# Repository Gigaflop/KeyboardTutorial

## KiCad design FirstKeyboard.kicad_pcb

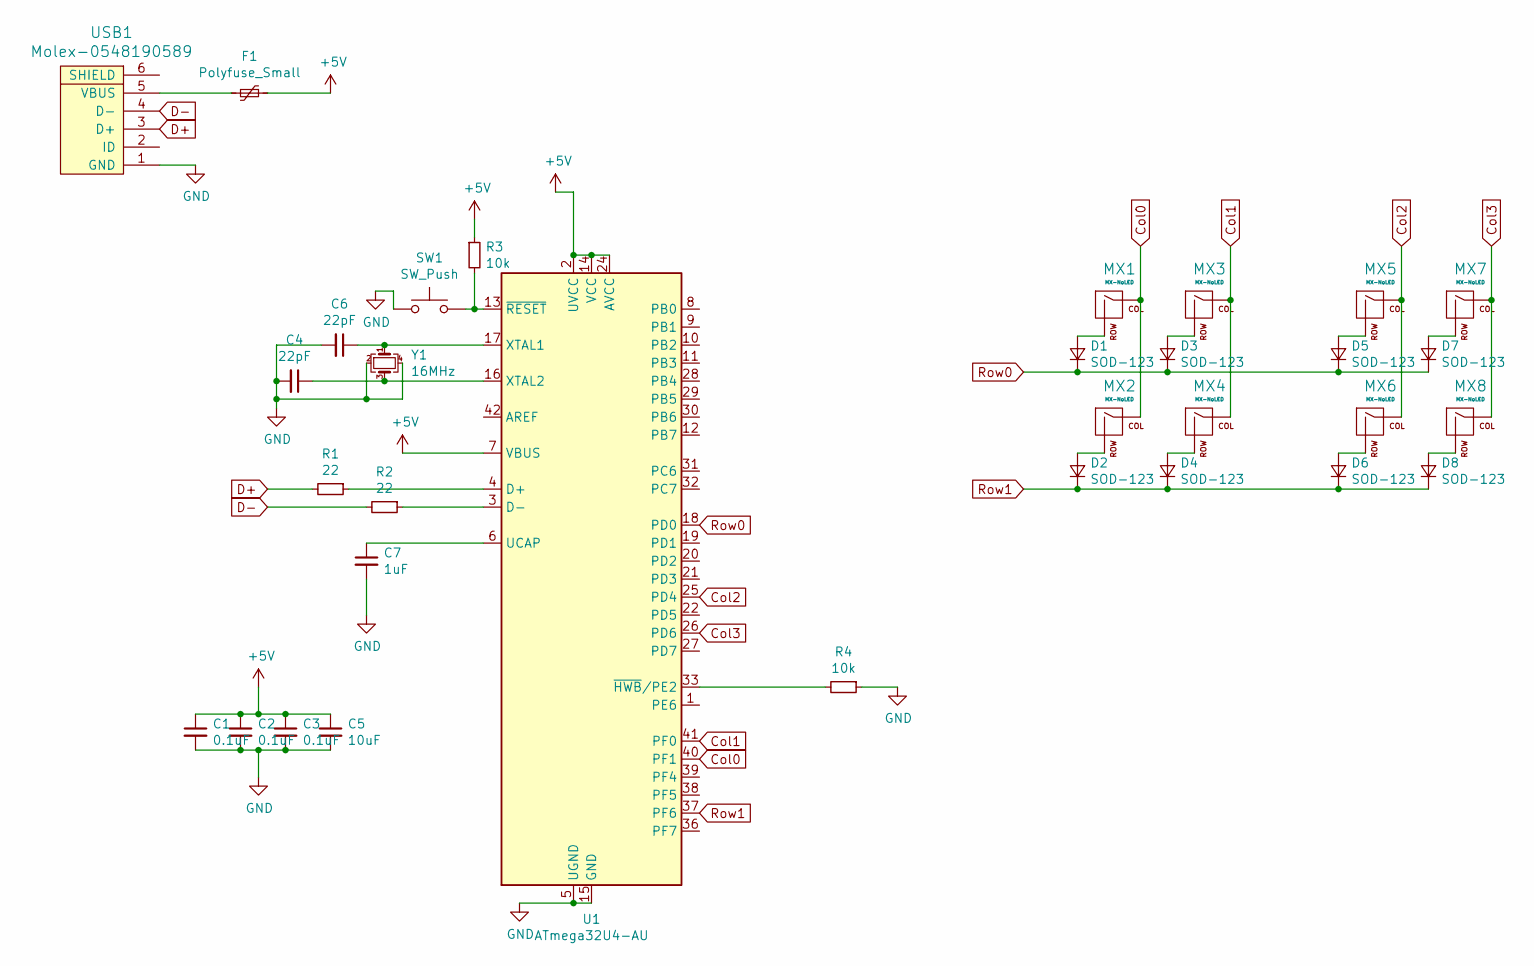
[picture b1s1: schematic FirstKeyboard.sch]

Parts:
C1, C2, C3: 0.1uF; C_0805_2012Metric
C4, C6: 22pF; C_0805_2012Metric
C5: 10uF; C_0805_2012Metric
C7: 1uF; C_0805_2012Metric
D1, D2, D3, D4, D5, D6, D7, D8: SOD-123; D_SOD-123
F1: Polyfuse_Small; Fuse_1206_3216Metric
MX1, MX2, MX3, MX4, MX5, MX6, MX7, MX8: MX-NoLED; MX-1U-NoLED
R1, R2: 22; R_0805_2012Metric
R3, R4: 10k; R_0805_2012Metric
SW1: SW_Push; SKQG-1155865
U1: ATmega32U4-AU; TQFP-44_10x10mm_P0.8mm
USB1: Molex-0548190589
Y1: 16MHz; Crystal_SMD_3225-4Pin_3.2x2.5mm

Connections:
+5V: C1.1, C2.1, C3.1, C5.1, F1.1, R3.1, U1.2 (UVCC), U1.7 (VBUS), U1.14 (VCC), U1.24 (AVCC), U1.34 (VCC), U1.44 (AVCC)
Col0: MX1.1 (COL), MX2.1 (COL), U1.40 (PF1)
Col1: MX3.1 (COL), MX4.1 (COL), U1.41 (PF0)
Col2: MX5.1 (COL), MX6.1 (COL), U1.25 (PD4)
Col3: MX7.1 (COL), MX8.1 (COL), U1.26 (PD6)
D+: R1.2, USB1.3 (D+)
D-: R2.2, USB1.4 (D-)
GND: C1.2, C2.2, C3.2, C4.2, C5.2, C6.2, C7.2, R4.1, SW1.1, U1.5 (UGND), U1.15 (GND), U1.23 (GND), U1.35 (GND), U1.43 (GND), USB1.1 (GND), Y1.2, Y1.4
unnamed: C4.1, U1.16 (XTAL2), Y1.3
unnamed: C6.1, U1.17 (XTAL1), Y1.1
unnamed: C7.1, U1.6 (UCAP)
unnamed: D1.2 (A), MX1.2 (ROW)
unnamed: D2.2 (A), MX2.2 (ROW)
unnamed: D3.2 (A), MX3.2 (ROW)
unnamed: D4.2 (A), MX4.2 (ROW)
unnamed: D5.2 (A), MX5.2 (ROW)
unnamed: D6.2 (A), MX6.2 (ROW)
unnamed: D7.2 (A), MX7.2 (ROW)
unnamed: D8.2 (A), MX8.2 (ROW)
unnamed: F1.2, USB1.5 (VBUS)
unnamed: R1.1, U1.4 (D+)
unnamed: R2.1, U1.3 (D-)
unnamed: R3.2, SW1.2, U1.13 (~RESET)
unnamed: R4.2, U1.33 (~HWB~/PE2)
Row0: D1.1 (K), D3.1 (K), D5.1 (K), D7.1 (K), U1.18 (PD0)
Row1: D2.1 (K), D4.1 (K), D6.1 (K), D8.1 (K), U1.37 (PF6)

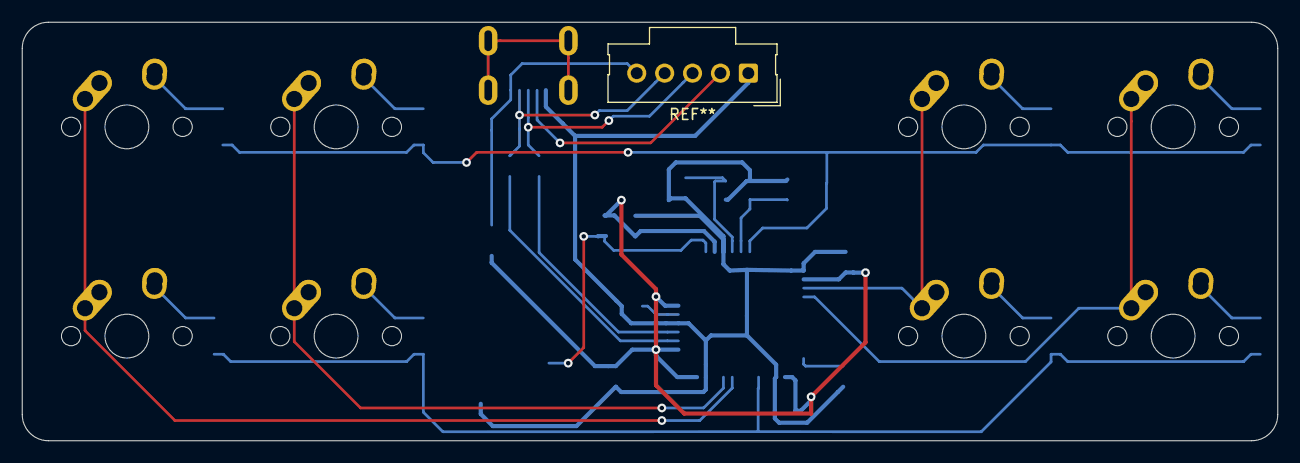
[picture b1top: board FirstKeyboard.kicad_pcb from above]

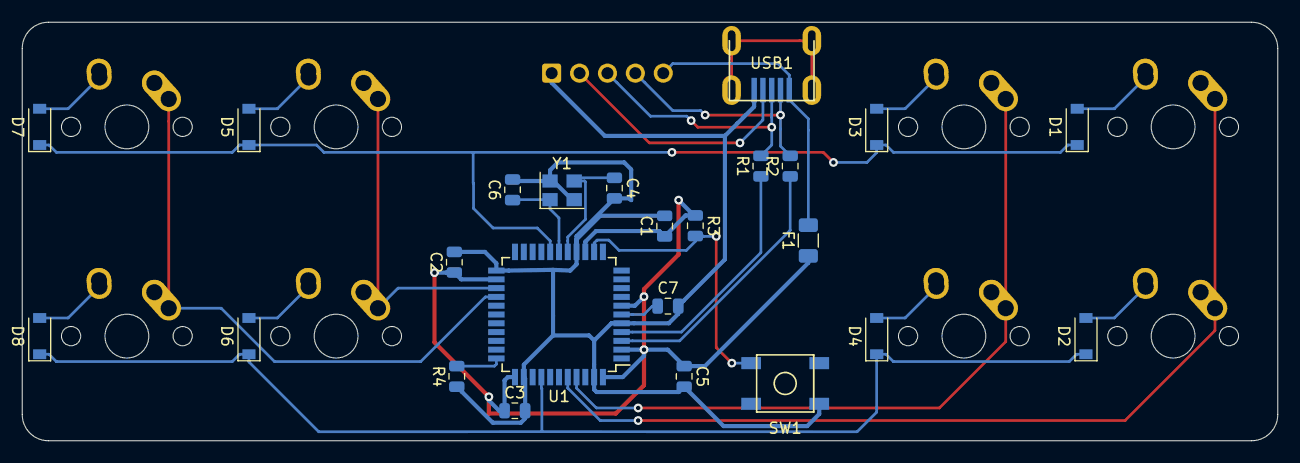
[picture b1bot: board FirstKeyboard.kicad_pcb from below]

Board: 2 copper layers, 114.3 x 38.1 mm, 32 parts (24 on the bottom side), 26 nets.

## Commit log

2020-04-04 added libraries in kicad
2020-04-04 added symbol tables
2020-04-04 added crystal + caps
2020-04-04 added reset switch
2020-04-04 Added switch matrix, and doubled it
2020-04-07 Added all untracked files. Mapped parts to footprints on Eeschema.
2020-04-09 Barfed out the pcb stuff, moved switch footprints to about where they should be
2020-04-09 Readjusted switch footprints to desired spacing of later project. Moved diodes on bottom side, within switch footprint area.
2020-04-09 oops, caps are labeled differently than tutorial. Gotta figure that out later.
2020-04-10 components should all be placed roughly appropriately, relative to each other. Will add holes for usb handwire later.
2020-04-10 added edge cuts, adjusted componenet layout slightly
2020-04-11 Added vias for USB breakout, hopefully. Routed all MCU traces. Next is routing Matrix traces.
2020-04-12 Added and mapped pads to breakout usb connector. Next is to remove vias and map row, col to mcu pins
2020-04-12 Added data tags for pins
2020-04-12 mapped r, c to pins and routed
2020-04-12 routed usb breakout
2020-04-14 fixed missing traces
